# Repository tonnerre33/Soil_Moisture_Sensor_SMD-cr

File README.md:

# Soil Moisture Sensor SMD

# What is this ?

Simple office plant monitor inspired by [@carlierd](https://www.openhardware.io/user/97/projects/carlierd) on the [this](https://www.openhardware.io/view/123/Office-plant-monitor) post.

This is my first SMD project, i hope he'll used by other members ;)

The skech is 2.0.0 Mysensors compatible, i haven't test this sketch with the 2.1.1 version.

You can order the pcb here : https://PCBs.io/share/zjX7M

The PCB files are for the V1.1.2 version, i haven't posted the V1.1 because there were important mistakes on the v1.1.

I have put 3 leds on this project :

* one connected on SCK for see the same thing than an arduino pro mini
* one for see when the node is initialised and when is goes in a sleep mode
* one not used for the moment, my idea was to use this led for offline node but i don't know how to do this without alterate the autonomie of the battery :(

# Features :

* Send Soil moisture mesure every hours
* Send Battery Level every hours if the value has changed
* Send Battery voltage every hours if the percentage has changed

# Compatibilies :

* Mysensors Library 2.0.0
* PCBs v1.1.x compatibles with Soil_Moisture_Sensor_SMD_v1.1.x sketchs

# Logs PCB :
## V1.1.2

* 16/02/2017 = Fabrication V1.1.2 by PCBs.io => Awaiting Panelization
* 20/02/2017 = Fabrication V1.1.2 by PCBs.io => In Fabrication
* 27/02/2017 = Fabrication V1.1.2 by PCBs.io => Shipped
* 09/03/2017 = Fabrication V1.1.2 by PCBs.io => Received
* 11/03/2017 = Assembly and Test => Functional Board but some minors issues => see v1.1.2a

## V1.1.2a
### minors modifications

* Increase Drill battery older CR123
* Modify text "FTDI" by "AVRISP"
* Add text "FTDI"

# Logs Sketch:
## V1.1.1

* Add default values
* Do not send moisture to the controler if she didn't change more than 1%
* Change Low Fuse example

## V1.1.2
* Fixed "Do not send moisture to the controler if she didn't change more than 1%"
* Added possibility to blink the "info" led when insufficient moisture
* Added possibility to blink the "warning" led when insufficient battery
* Added possibility to use this node without controler (need mysensors >= 2.1.0)
* Disable smartsleep when not OTA used (increase battery life)

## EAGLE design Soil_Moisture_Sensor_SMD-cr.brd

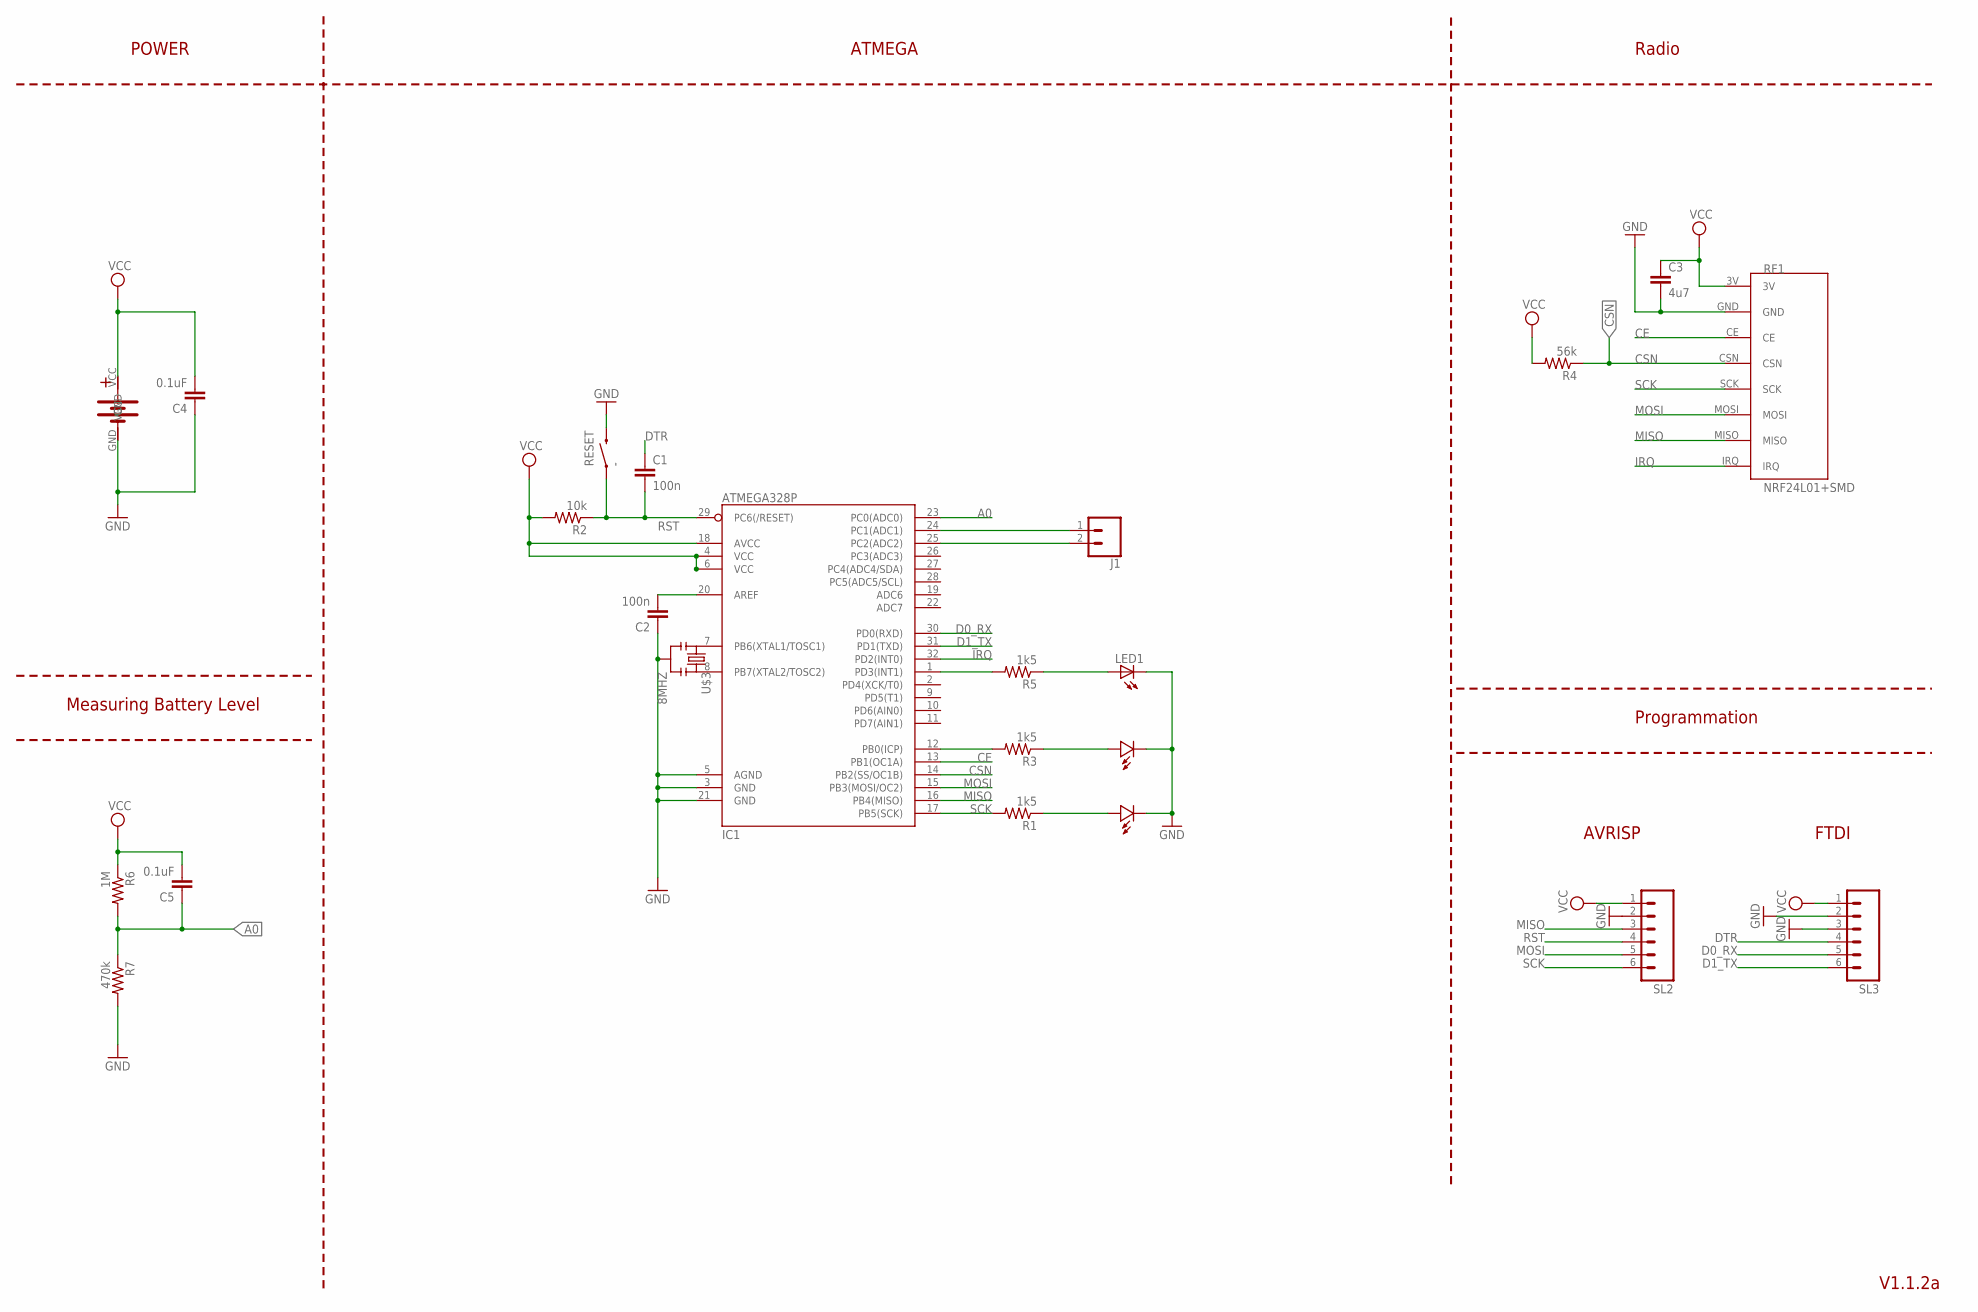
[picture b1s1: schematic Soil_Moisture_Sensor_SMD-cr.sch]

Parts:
C1, C2: 100n; 0805-CAP
C3: 4u7; 0805-CAP
C4, C5: 0.1uF; 0805-CAP
D1, D2: LED0805; 0805-LED
IC1: ATMEGA328P; TQFP32-08
J1: CONN_02; 1X02
LED1: LED5MM
R1, R3, R5: 1k5; 0805-RES
R2: 10k; 0805-RES
R4: 56k; 0805-RES
R6: 1M; 0805-RES
R7: 470k; 0805-RES
RESET: -; TACTILE-SWITCH-1101NE
RF1: NRF24L01+SMD; NRF24L01+SMD_MODULE
SL2, SL3: M06SMD-1MM; 1X06-1MM
U$1: CR123-BATTERYHOLDER; CR123_BATTERYHOLDER
U$3: 8MHZ; RESONATOR-SMD

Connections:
A0: C5.1, IC1.23 (PC0(ADC0)), R6.2, R7.1
CE: IC1.13 (PB1(OC1A)), RF1.CE
CSN: IC1.14 (PB2(SS/OC1B)), R4.1, RF1.CSN
D0_RX: IC1.30 (PD0(RXD)), SL3.5
D1_TX: IC1.31 (PD1(TXD)), SL3.6
DTR: C1.1, SL3.4
GND: C2.1, C3.2, C4.1, D1.MINUS, D2.MINUS, IC1.3 (GND), IC1.5 (AGND), IC1.21 (GND), LED1.K (C), R7.2, RESET.P$2 (2), RF1.GND, SL2.2, SL3.2, SL3.3, U$1.GND, U$3.2
IRQ: IC1.32 (PD2(INT0)), RF1.IRQ
MISO: IC1.16 (PB4(MISO)), RF1.MISO, SL2.3
MOSI: IC1.15 (PB3(MOSI/OC2)), RF1.MOSI, SL2.5
unnamed: D2.PLUS, R1.1
unnamed: IC1.7 (PB6(XTAL1/TOSC1)), U$3.1
unnamed: IC1.25 (PC2(ADC2)), J1.2
unnamed: C2.2, IC1.20 (AREF)
unnamed: IC1.24 (PC1(ADC1)), J1.1
unnamed: IC1.12 (PB0(ICP)), R3.2
unnamed: D1.PLUS, R3.1
unnamed: IC1.8 (PB7(XTAL2/TOSC2)), U$3.3
unnamed: IC1.1 (PD3(INT1)), R5.2
unnamed: LED1.A, R5.1
RST: C1.2, IC1.29 (PC6(/RESET)), R2.1, RESET.P$1 (1), SL2.4
SCK: IC1.17 (PB5(SCK)), R1.2, RF1.SCK, SL2.6
VCC: C3.1, C4.2, C5.2, IC1.4 (VCC), IC1.6 (VCC), IC1.18 (AVCC), R2.2, R4.2, R6.1, RF1.3V, SL2.1, SL3.1, U$1.VCC

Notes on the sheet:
Programmation
FTDI
AVRISP
Radio
ATMEGA
POWER
Measuring Battery Level
V1.1.2a

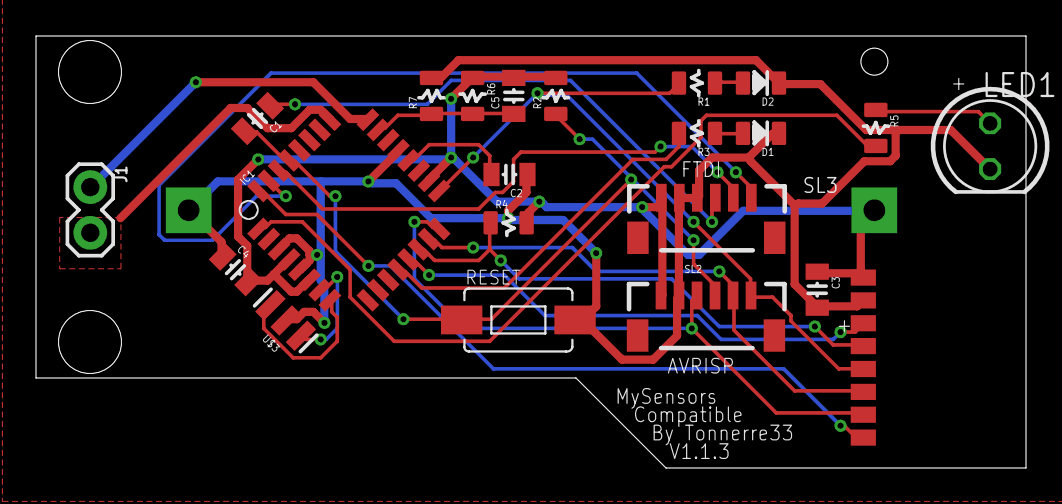
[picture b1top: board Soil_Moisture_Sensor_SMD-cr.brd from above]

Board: 2 copper layers, 55.0 x 24.0 mm, 23 parts (1 on the bottom side), 23 nets.

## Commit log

2017-03-18 pcb-v1.1.2a
2017-03-18 fw-v1.1.1
2017-03-19 fw-v1.1.2
2017-03-19 fw-1.1.2
2017-03-19 fw-1.1.2 Move LED PIN info in presentation for compatibility with mysensors >2.1.0
2017-04-15 53x20
2017-04-15 pcb-v1.1.3
2017-08-24 update png and pdf
2017-08-29 correct values sleepTime
2017-08-29 v1.1.3
2017-08-29 change def WARN_TIME
2017-08-29 Disable Debug and Node_without_gateway by default
2017-09-23 correct mode without gateway & auto indent code
2017-09-23 auto indent
